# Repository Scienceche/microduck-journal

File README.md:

# 🦆 复刻 Microduck —— 项目日志仓库

对 [fanhao375/microduck-replica](https://github.com/fanhao375/microduck-replica) /
[OSHWhub imu_to_servo 团购板](https://oshwhub.com/team_wijnbslh/project_jhgdebrg) 的复刻实作记录：
一块自己焊的 IMU 总线板（STM32G031 + LSM6DSV16X + SN74LVC2G241）、一个 Radxa Zero 3W 主控、
15 颗飞特 HD1910、自训 RL 步态策略，以及把这一切调通的全部血泪。

> 私人仓库 · 每日自动同步自工作目录 `E:\c1349\复刻microduck`

## 当前状态（2026-11-06）

| 子系统 | 状态 |
|---|---|
| IMU 板（总线从机 ID 200 @1Mbps，FT6 协议） | ✅ 完全工作，装向四元数实测校准至 0.00° |
| 固件栈 | ✅ kissqy 官方栈 robotd 0.15.1（control.43）+ 三轮交叉编译热修复 |
| 总线质量 | ✅ 丢包 6-9% → 0.004%（ID12/13、ID34→10 两处时隙碰撞已断开） |
| 整机标定 | ✅ 15 舵机零位/方向/限位（标定台 :8085，robotd 桥接） |
| RL 训练（mjlab/MuJoCo Warp） | ✅ walk5 前进 0.19m/s；VelStand 抗扰站立 99% 存活（未部署） |
| 仿真保真 | ✅ 936g 整机质量 + 202g 电池（**含碰撞盒 70×38×35mm**，2026-11-06 起） |
| 步态/站立（kissqy 自训模型） | ✅ 满电+校向后 10 次冲击（翻滚/前冲/侧切/旋转）不倒 |
| 起身恢复 | ⏳ 测试中：门卫链路已打通，待满电跑 5 次推倒统计 |
| 摄像头（IMX219 CSI） | ✅ 单帧验证通过；mediad WebRTC 待装 GStreamer 栈 |
| 电源 | ⚠️ 2S 软包（7.72V@今晨）；峰值曾拉穿电压致整机重启，起身测试需满电 |

## 目录

```
docs/        调试记录（最重要的文件——完整故障树与修复过程）
firmware/    imu-to-ttl 固件（STM32G031 裸机，make g031-dxl）
hardware/    KiCad 复刻工程 + 元件手册
panel/       中控面板 duck_panel（旧栈）+ calib-panel 标定台（:8085，robotd 桥接）
sync.sh      每日同步脚本（工作目录 → 本仓库 → GitHub）
```

## 硬件速查

- **IMU 板**：团购 PCB + 克隆 STM32G031F8P6 + LSM6DSV16X（换过一颗，旧颗其实没坏）
- **舵机**：飞特 HD1910 ×15，ID 10-14 右腿 / 20-24 左腿 / 30-34 颈头嘴，IMU=200
- **接线**：imu-to-ttl 板自带 4 路舵机总线口 J_L/J_R/J_NECK/J_HEAD（丝印），比外接 hub 电流路径更均衡；
  dxl_hub（3 口无源）留作备用
- **电池**：2S 软包 70×38×35mm + 底座共 202g，装于躯干后下 (-0.027, 0, -0.055)；仿真已含碰撞盒
- 总线：飞特协议 1Mbps 半双工；U3=SN74LVC2G241（注意：**4脚是GND**，3脚=RX出，6脚=TX出）
- 已知坑：克隆 MCU 的 USART **DEM 硬件无效**（固件用软件 DE）；克隆批次 IMU 的 **SFLP 引擎输出乱转**
  （固件改软件 Mahony）；PB8/BOOT0 悬空随机进 bootloader（10k 拉带解决）

## 关键教训（详见调试记录）

1. 两层显示假象叠加可以完美伪装成"传感器坏轴"——用原始字节对质，不要信中间层
2. Mahony 积分项必须与比例项**同号相加**；接反=正反馈发散（主机回放 30 秒实锤）
3. 照抄参考代码写寄存器时，**核对每个地址和值的字面常量**（IF_CFG 0x02≠0x03 害人一整天）
4. 克隆 J-Link 自报产品名 "MS-ARGB"；WinUSB/WCID 一直在正常工作
5. Sync Read 相邻 ID 存在**应答时隙碰撞**（12→13、34→10 两处）：下一 ID 提前 1-2 比特应答污染上一 ID
   校验和。回包按 ID 解码与包序无关——换包序即可修复，硬件无需动
6. 仿真加配重**必须同时加碰撞几何**：只焊质量不焊盒子，策略对物理障碍"无感"，真机上脚怼进电池
7. IMU 装向校验要看**全重力向量**：gz 在小角度下与 0° 无异（cos8°=0.990），gx/gy 才暴露偏差
8. robotd 的标定/运动模式写进 systemd drop-in，**重启会继承**——"策略没反应"先查模式；
   init 不是起身控制器，趴姿 init 起不来

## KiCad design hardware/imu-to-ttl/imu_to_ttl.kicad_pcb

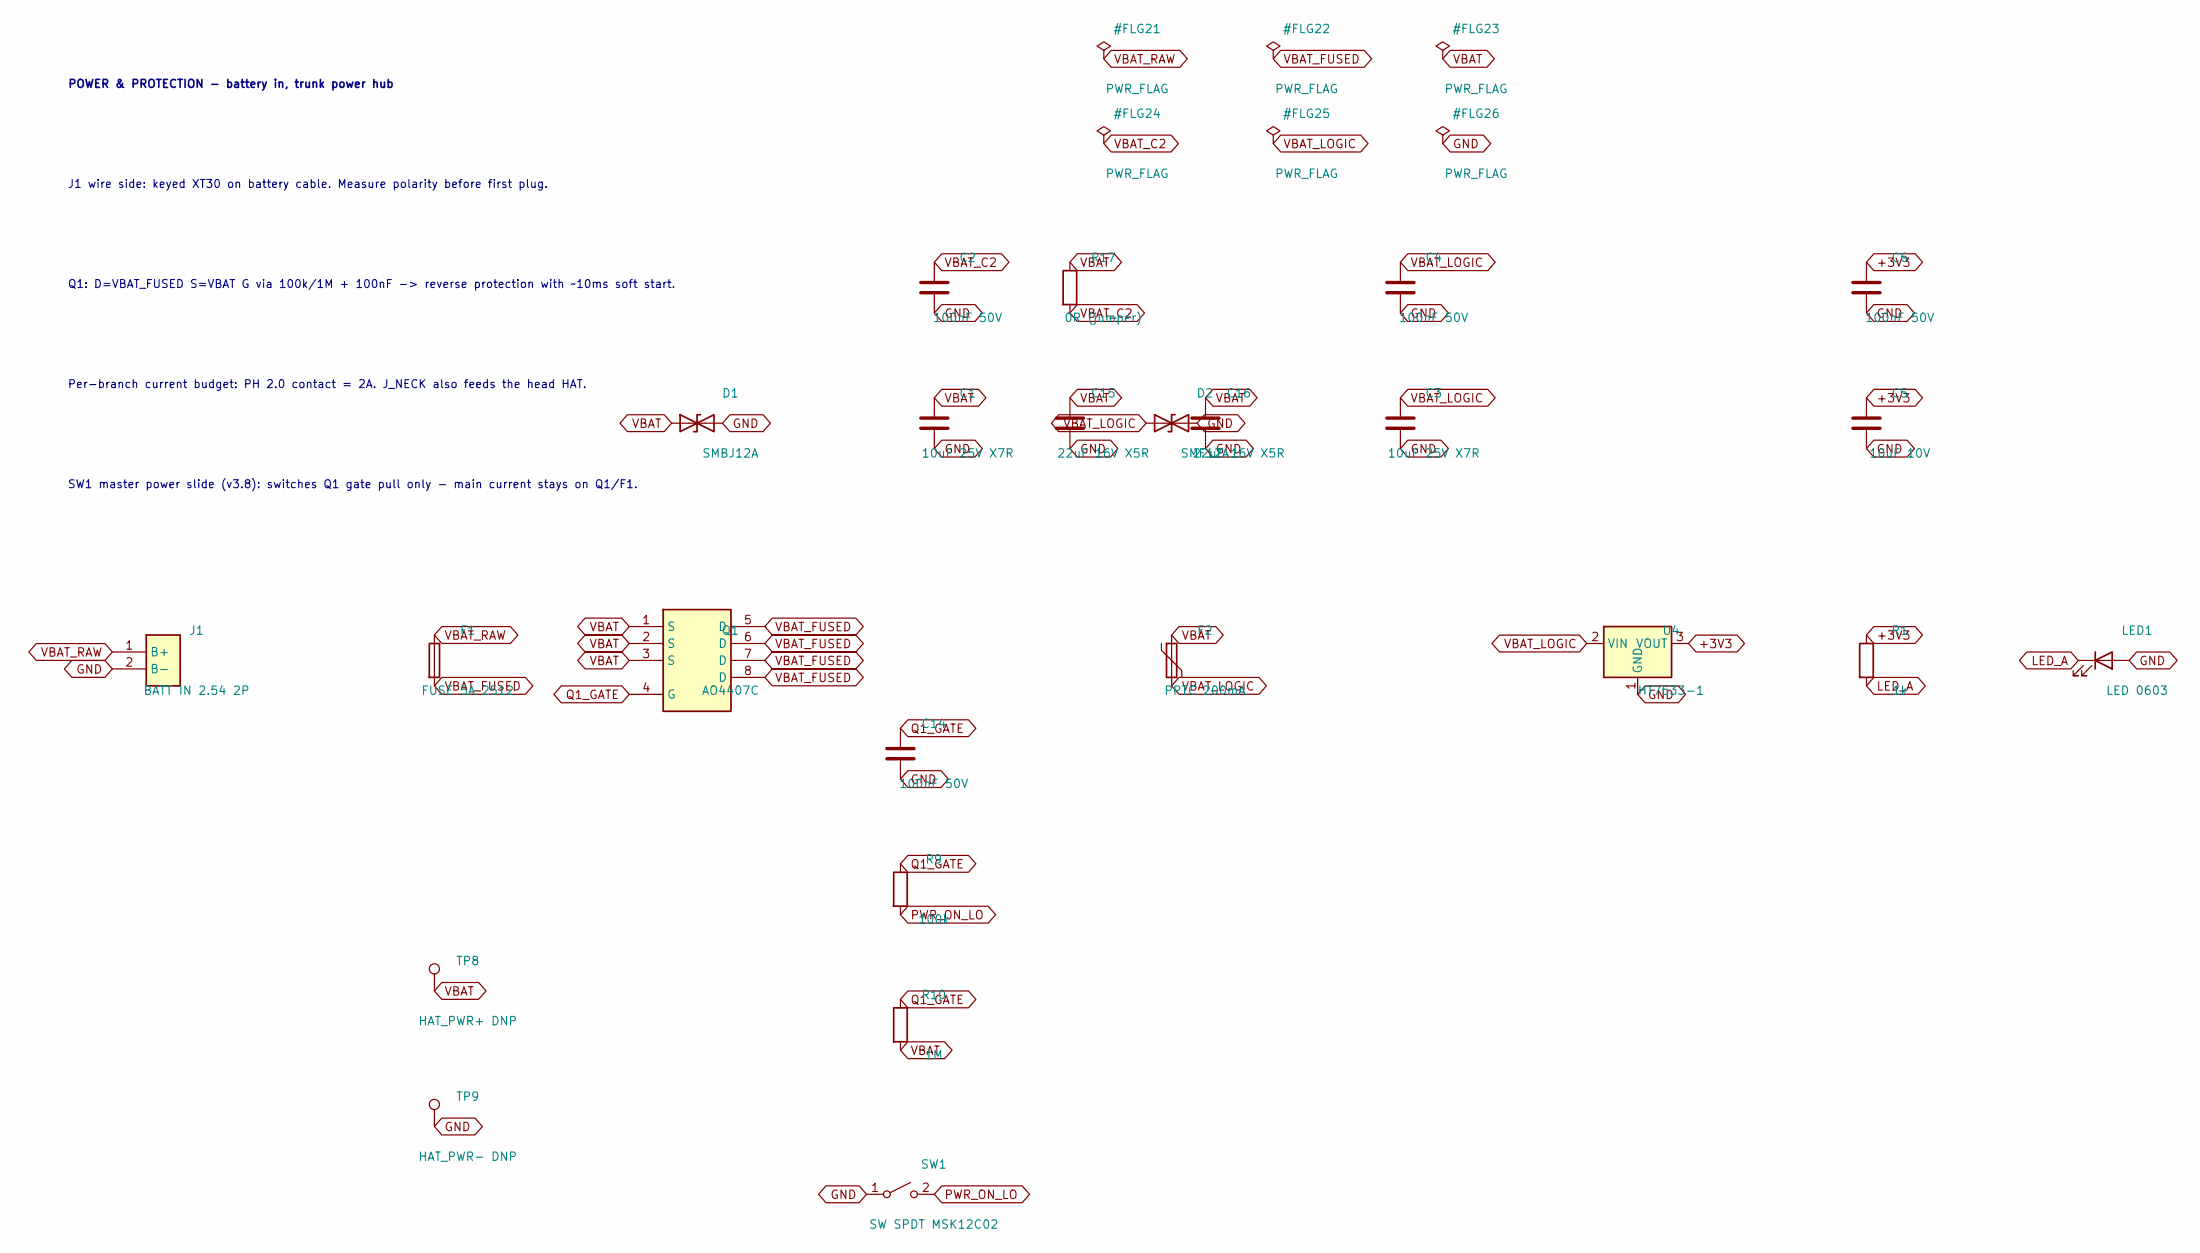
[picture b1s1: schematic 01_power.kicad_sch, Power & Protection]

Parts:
C1: 10uF 25V X7R; C_1206_3216Metric; MPN GRM31CR71E106KA12L; LCSC C77093
C2, C4, C6, C14: 100nF 50V; C_0603_1608Metric; MPN CC0603KRX7R9BB104; LCSC C14663
C3: 10uF 25V X7R; C_0805_2012Metric; MPN GRM31CR71E106KA12L; LCSC C77093
C5: 10uF 10V; C_0603_1608Metric; MPN CL10A106KP8NNNC; LCSC C19702
C15, C16: 22uF 16V X5R; C_1210_3225Metric; MPN EMK325BJ226KMHP; LCSC C359910
D1: SMBJ12A; D_SMB; MPN SMBJ12A/TR13; LCSC C111091
D2: SMF12A; D_SOD-123F; MPN SMF12A; LCSC C2943870
F1: FUSE 5A 2512; Fuse_1206_3216Metric; MPN 0466005.NRHF; LCSC C57525
F2: PPTC 200mA; Fuse_1206_3216Metric; MPN MF-NSMF020X-2; LCSC C210358
J1: BATT IN 2.54 2P; BattPad_1x02_P3.60mm_Drill1.2mm
LED1: LED 0603; LED_0603_1608Metric; MPN KT-0603R; LCSC C2286
Q1: AO4407C; SOIC-8_3.9x4.9mm_P1.27mm; MPN AO4407C; LCSC C469397
R1: 1k; R_0603_1608Metric; MPN 0603WAF1001T5E; LCSC C21190
R9: 100k; R_0603_1608Metric; MPN 0603WAF1003T5E; LCSC C25803
R10: 1M; R_0603_1608Metric; MPN 0603WAF1004T5E; LCSC C22935
R17: 0R (jumper); R_0603_1608Metric
SW1: SW SPDT MSK12C02; SW_SPDT_Shouhan_MSK12C02; MPN MSK12C02-LG; LCSC C431537
TP8: HAT_PWR+ DNP; TestPoint_Pad_D1.5mm
TP9: HAT_PWR- DNP; TestPoint_Pad_D1.5mm
U4: HT7533-1; SOT-89-3; MPN HT7533-1; LCSC C14289

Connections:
+3V3: C5.1, C6.1, R1.1, U4.3 (VOUT); also elsewhere on the board
GND: C1.2, C2.2, C3.2, C4.2, C5.2, C6.2, C14.2, C15.2, C16.2, D1.2 (A2), D2.2 (A2), J1.2 (B-), LED1.2 (A), SW1.1 (A), TP9.1, U4.1 (GND); also elsewhere on the board
LED_A: LED1.1 (K), R1.2
PWR_ON_LO: R9.2, SW1.2 (B)
Q1_GATE: C14.1, Q1.4 (G), R9.1, R10.1
VBAT: C1.1, C15.1, C16.1, D1.1 (A1), F2.1, Q1.1 (S), Q1.2 (S), Q1.3 (S), R10.2, R17.1, TP8.1; also elsewhere on the board
VBAT_C2: C2.1, R17.2
VBAT_FUSED: F1.2, Q1.5 (D), Q1.6 (D), Q1.7 (D), Q1.8 (D)
VBAT_LOGIC: C3.1, C4.1, D2.1 (A1), F2.2, U4.2 (VIN)
VBAT_RAW: F1.1, J1.1 (B+)

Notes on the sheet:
POWER & PROTECTION - battery in, trunk power hub
J1 wire side: keyed XT30 on battery cable. Measure polarity before first plug.
Q1: D=VBAT_FUSED S=VBAT G via 100k/1M + 100nF -> reverse protection with ~10ms soft start.
Per-branch current budget: PH 2.0 contact = 2A. J_NECK also feeds the head HAT.
SW1 master power slide (v3.8): switches Q1 gate pull only - main current stays on Q1/F1.

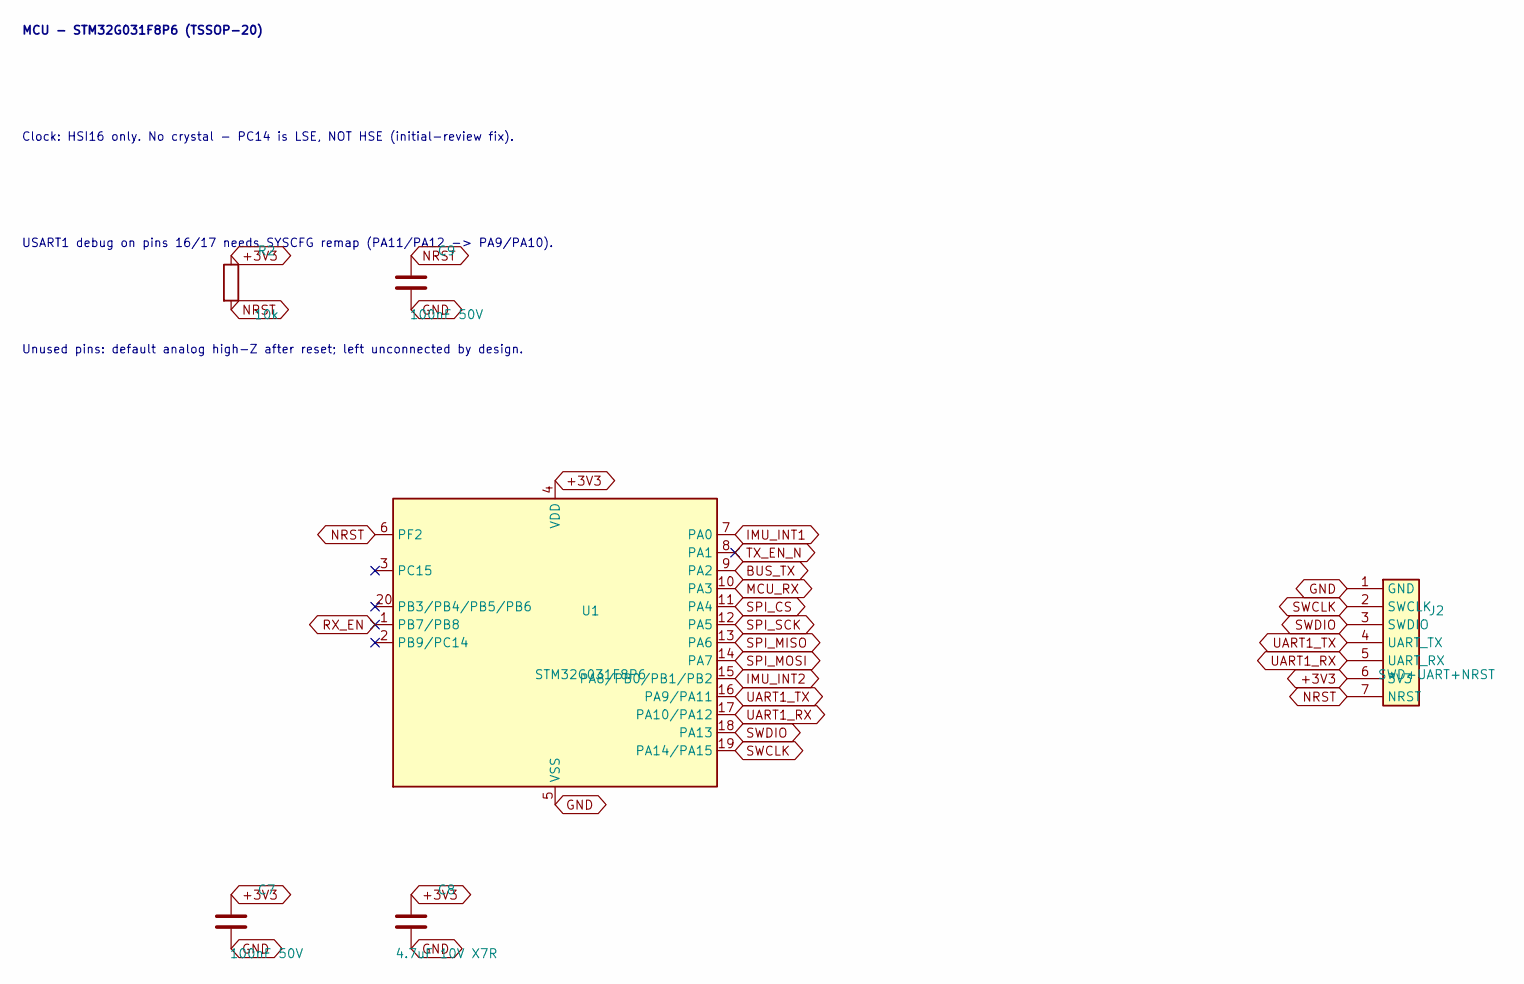
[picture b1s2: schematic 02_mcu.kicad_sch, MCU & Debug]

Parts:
C7, C9: 100nF 50V; C_0603_1608Metric; MPN CC0603KRX7R9BB104; LCSC C14663
C8: 4.7uF 10V X7R; C_0603_1608Metric; MPN CL10A475KO8NNNC; LCSC C19666
J2: SWD+UART+NRST; PinHeader_1x07_P2.54mm_Vertical; MPN PZ254R-11-07P; LCSC C492415
R2: 10k; R_0603_1608Metric; MPN 0603WAF1002T5E; LCSC C25804
U1: STM32G031F8P6; TSSOP-20_4.4x6.5mm_P0.65mm; MPN STM32G031F8P6; LCSC C529334

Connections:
+3V3: C7.1, C8.1, J2.6 (3V3), R2.1, U1.4 (VDD); also elsewhere on the board
BUS_TX: U1.9 (PA2); also elsewhere on the board
GND: C7.2, C8.2, C9.2, J2.1 (GND), U1.5 (VSS); also elsewhere on the board
IMU_INT1: U1.7 (PA0); also elsewhere on the board
IMU_INT2: U1.15 (PA8/PB0/PB1/PB2); also elsewhere on the board
MCU_RX: U1.10 (PA3); also elsewhere on the board
NRST: C9.1, J2.7 (NRST), R2.2, U1.6 (PF2)
RX_EN: U1.1 (PB7/PB8); also elsewhere on the board
SPI_CS: U1.11 (PA4); also elsewhere on the board
SPI_MISO: U1.13 (PA6); also elsewhere on the board
SPI_MOSI: U1.14 (PA7); also elsewhere on the board
SPI_SCK: U1.12 (PA5); also elsewhere on the board
SWCLK: J2.2 (SWCLK), U1.19 (PA14/PA15)
SWDIO: J2.3 (SWDIO), U1.18 (PA13)
TX_EN_N: U1.8 (PA1); also elsewhere on the board
UART1_RX: J2.5 (UART_RX), U1.17 (PA10/PA12)
UART1_TX: J2.4 (UART_TX), U1.16 (PA9/PA11)

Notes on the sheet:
MCU - STM32G031F8P6 (TSSOP-20)
Clock: HSI16 only. No crystal - PC14 is LSE, NOT HSE (initial-review fix).
USART1 debug on pins 16/17 needs SYSCFG remap (PA11/PA12 -> PA9/PA10).
Unused pins: default analog high-Z after reset; left unconnected by design.

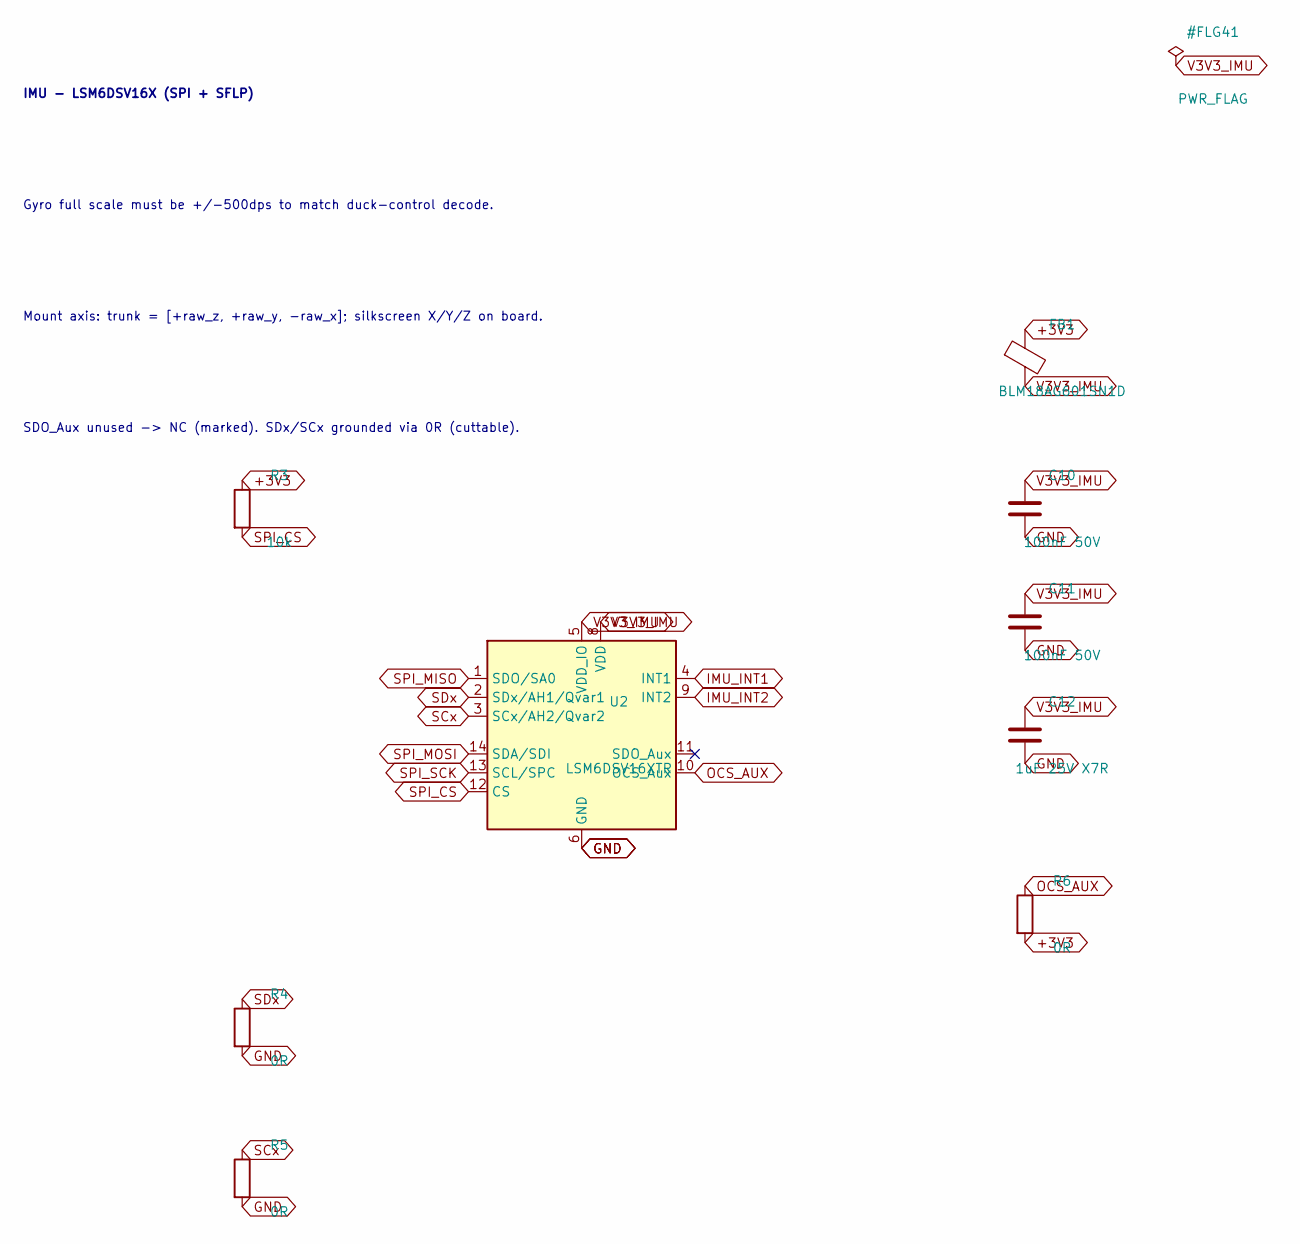
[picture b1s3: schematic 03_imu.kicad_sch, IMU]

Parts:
C10, C11: 100nF 50V; C_0603_1608Metric; MPN CC0603KRX7R9BB104; LCSC C14663
C12: 1uF 25V X7R; C_0603_1608Metric; MPN CL10B105KA8NNNC; LCSC C29936
FB1: BLM18AG601SN1D; L_0603_1608Metric; MPN BLM18AG601SN1D; LCSC C19330
R3: 10k; R_0603_1608Metric; MPN 0603WAF1002T5E; LCSC C25804
R4, R5, R6: 0R; R_0603_1608Metric; MPN 0603WAF0000T5E; LCSC C21189
U2: LSM6DSV16XTR; ST_LGA14_3x2.5_P0.5_LSM6DSV16X_TN0018; MPN LSM6DSV16XTR; LCSC C5267406

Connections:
+3V3: FB1.1, R3.1, R6.2; also elsewhere on the board
GND: C10.2, C11.2, C12.2, R4.2, R5.2, U2.6 (GND), U2.7 (GND); also elsewhere on the board
IMU_INT1: U2.4 (INT1); also elsewhere on the board
IMU_INT2: U2.9 (INT2); also elsewhere on the board
OCS_AUX: R6.1, U2.10 (OCS_Aux)
SCx: R5.1, U2.3 (SCx/AH2/Qvar2)
SDx: R4.1, U2.2 (SDx/AH1/Qvar1)
SPI_CS: R3.2, U2.12 (CS); also elsewhere on the board
SPI_MISO: U2.1 (SDO/SA0); also elsewhere on the board
SPI_MOSI: U2.14 (SDA/SDI); also elsewhere on the board
SPI_SCK: U2.13 (SCL/SPC); also elsewhere on the board
V3V3_IMU: C10.1, C11.1, C12.1, FB1.2, U2.5 (VDD_IO), U2.8 (VDD)

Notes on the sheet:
IMU - LSM6DSV16X (SPI + SFLP)
Gyro full scale must be +/-500dps to match duck-control decode.
Mount axis: trunk = [+raw_z, +raw_y, -raw_x]; silkscreen X/Y/Z on board.
SDO_Aux unused -> NC (marked). SDx/SCx grounded via 0R (cuttable).

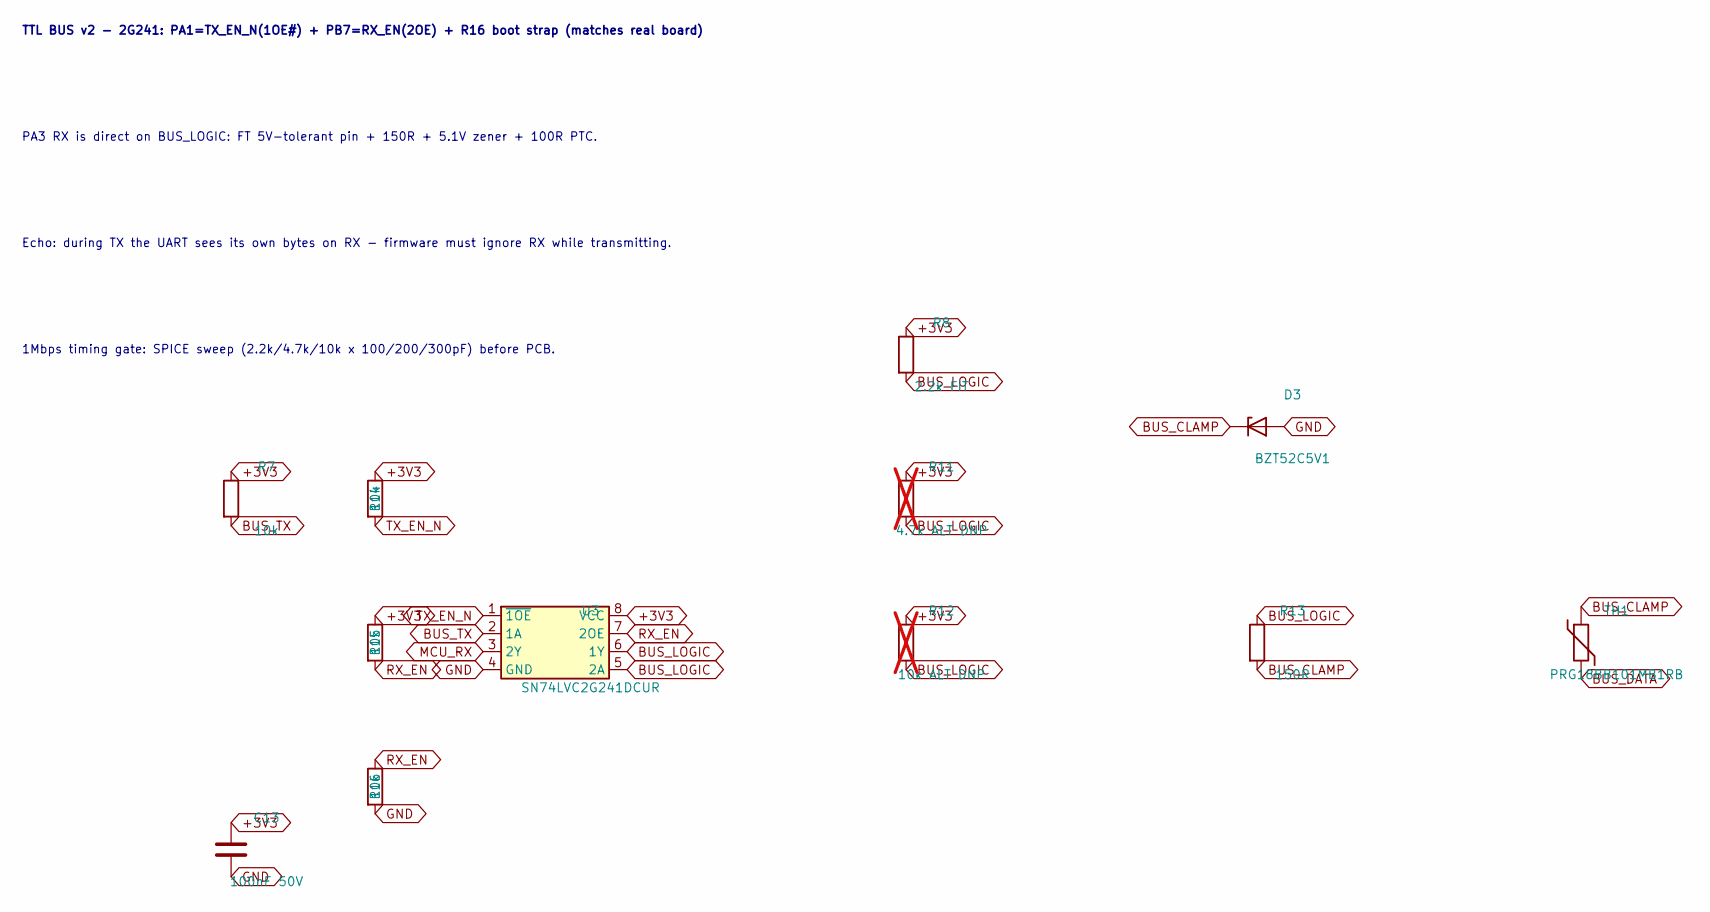
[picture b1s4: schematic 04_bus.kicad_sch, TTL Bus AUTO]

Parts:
C13: 100nF 50V; C_0603_1608Metric; MPN CC0603KRX7R9BB104; LCSC C14663
D3: BZT52C5V1; D_SOD-323; MPN BZT52C5V1-7-F; LCSC C151588
R7: 10k; R_0603_1608Metric; MPN 0603WAF1002T5E; LCSC C25804
R8: 2.2k FIT; R_0603_1608Metric; MPN 0603WAF2201T5E; LCSC C4190
R11: 4.7k ALT DNP; R_0603_1608Metric; MPN 0603WAF4701T5E; LCSC C23162; not fitted
R12: 10k ALT DNP; R_0603_1608Metric; MPN 0603WAF1002T5E; LCSC C25804; not fitted
R13: 150R; R_0603_1608Metric; MPN 0603WAF1500T5E; LCSC C22808
R14, R15, R16: 10k; R_0603_1608Metric
TH1: PRG18BB101MB1RB; R_0603_1608Metric; MPN PRG18BB101MB1RB; LCSC C913703
U3: SN74LVC2G241DCUR; VSSOP-8_2.3x2mm_P0.5mm; MPN SN74LVC2G241DCUR; LCSC C10430

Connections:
+3V3: C13.1, R7.1, R8.1, R11.1, R12.1, R14.1, R15.1, U3.8 (VCC); also elsewhere on the board
BUS_CLAMP: D3.1 (K), R13.2, TH1.1
BUS_DATA: TH1.2; also elsewhere on the board
BUS_LOGIC: R8.2, R11.2, R12.2, R13.1, U3.5 (2A), U3.6 (1Y)
BUS_TX: R7.2, U3.2 (1A); also elsewhere on the board
GND: C13.2, D3.2 (A), R16.2, U3.4 (GND); also elsewhere on the board
MCU_RX: U3.3 (2Y); also elsewhere on the board
RX_EN: R15.2, R16.1, U3.7 (2OE); also elsewhere on the board
TX_EN_N: R14.2, U3.1 (~1OE); also elsewhere on the board

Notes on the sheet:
TTL BUS v2 - 2G241: PA1=TX_EN_N(1OE#) + PB7=RX_EN(2OE) + R16 boot strap (matches real board)
PA3 RX is direct on BUS_LOGIC: FT 5V-tolerant pin + 150R + 5.1V zener + 100R PTC.
Echo: during TX the UART sees its own bytes on RX - firmware must ignore RX while transmitting.
1Mbps timing gate: SPICE sweep (2.2k/4.7k/10k x 100/200/300pF) before PCB.

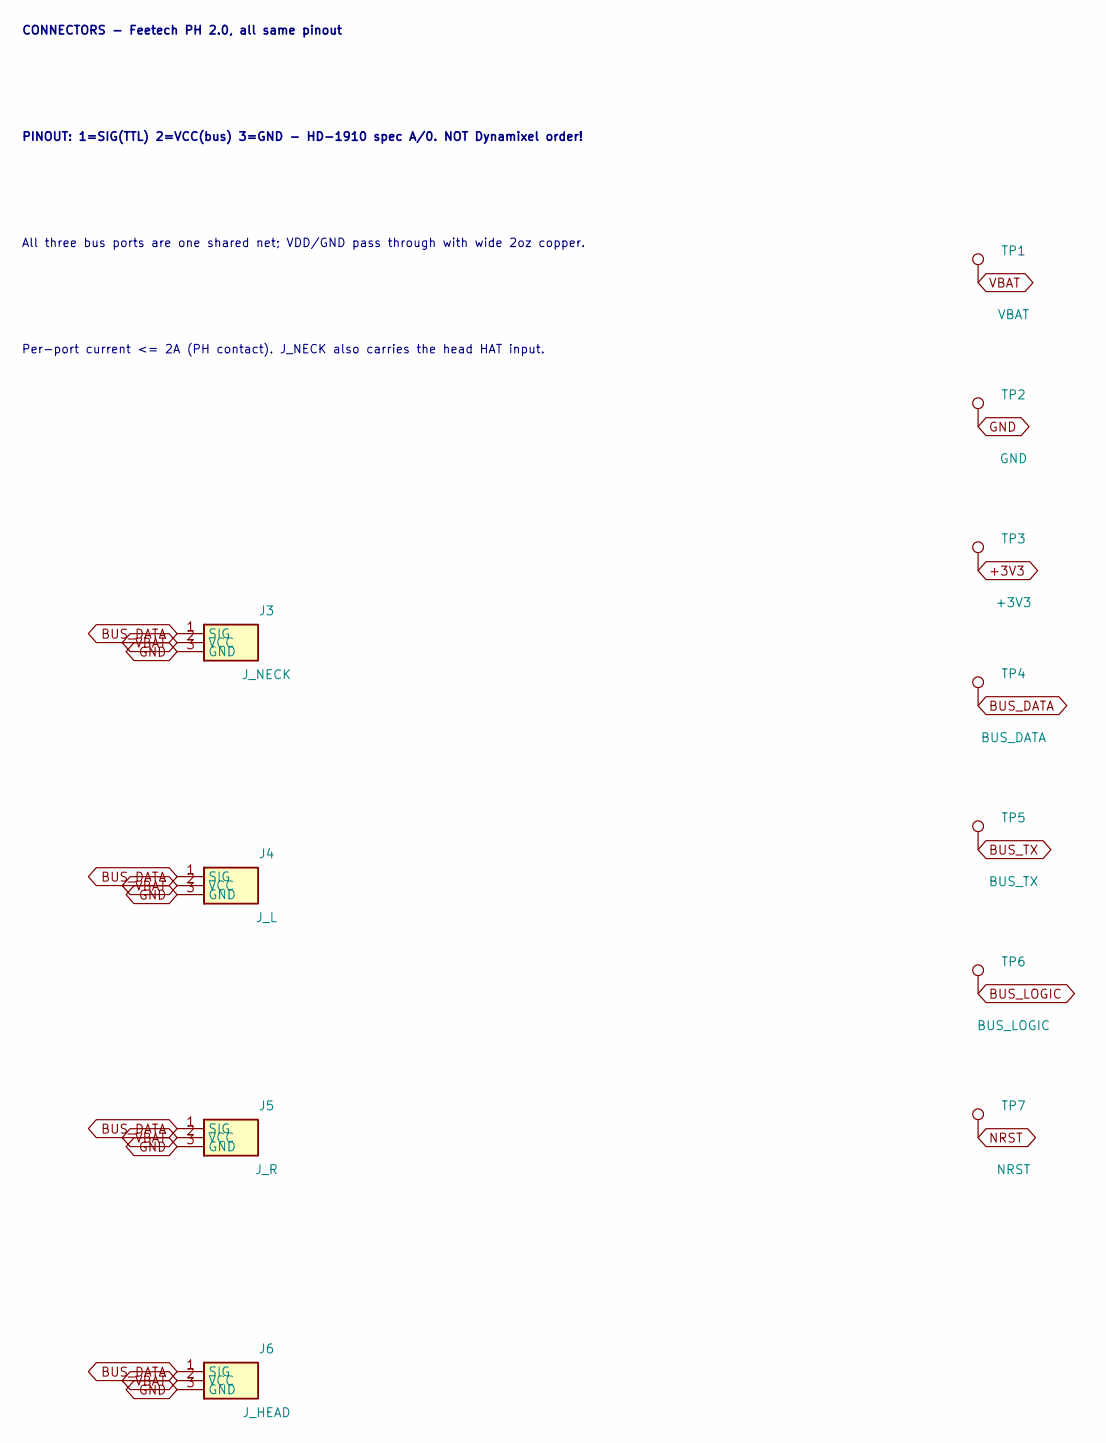
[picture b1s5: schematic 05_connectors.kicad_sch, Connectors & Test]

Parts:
J3: J_NECK; CONN-TH_B3B-PH-K-S; MPN B3B-PH-K-S(LF)(SN); LCSC C131339
J4: J_L; CONN-TH_S3B-PH-K-S; MPN S3B-PH-K-S(LF)(SN); LCSC C169277
J5: J_R; CONN-TH_S3B-PH-K-S; MPN S3B-PH-K-S(LF)(SN); LCSC C169277
J6: J_HEAD; CONN-TH_B3B-PH-K-S; MPN B3B-PH-K-S(LF)(SN); LCSC C131339
TP1: VBAT; TestPoint_Pad_D1.0mm
TP2: GND; TestPoint_Pad_D1.0mm
TP3: +3V3; TestPoint_Pad_D1.0mm
TP4: BUS_DATA; TestPoint_Pad_D1.0mm
TP5: BUS_TX; TestPoint_Pad_D1.0mm
TP6: BUS_LOGIC; TestPoint_Pad_D1.0mm
TP7: NRST; TestPoint_Pad_D1.0mm

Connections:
+3V3: TP3.1; also elsewhere on the board
BUS_DATA: J3.1 (SIG), J4.1 (SIG), J5.1 (SIG), J6.1 (SIG), TP4.1; also elsewhere on the board
GND: J3.3 (GND), J4.3 (GND), J5.3 (GND), J6.3 (GND), TP2.1; also elsewhere on the board
VBAT: J3.2 (VCC), J4.2 (VCC), J5.2 (VCC), J6.2 (VCC), TP1.1; also elsewhere on the board

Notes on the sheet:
CONNECTORS - Feetech PH 2.0, all same pinout
PINOUT: 1=SIG(TTL) 2=VCC(bus) 3=GND - HD-1910 spec A/0. NOT Dynamixel order!
All three bus ports are one shared net; VDD/GND pass through with wide 2oz copper.
Per-port current <= 2A (PH contact). J_NECK also carries the head HAT input.

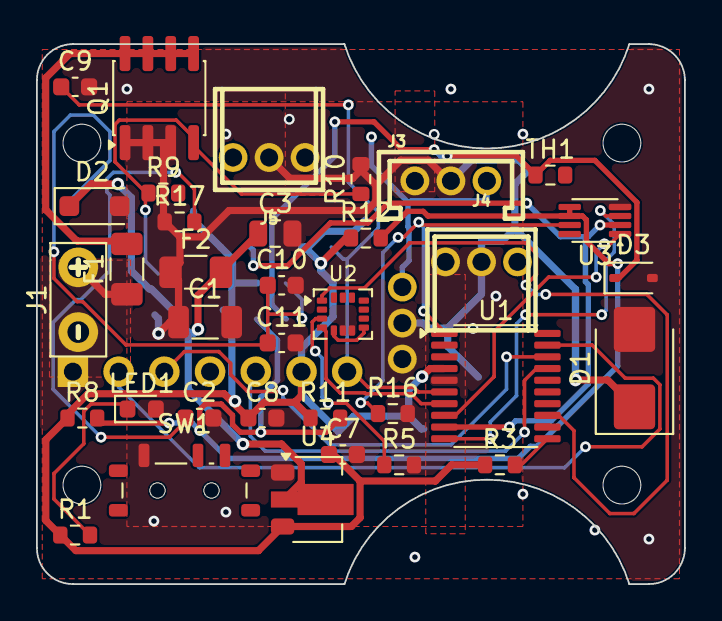
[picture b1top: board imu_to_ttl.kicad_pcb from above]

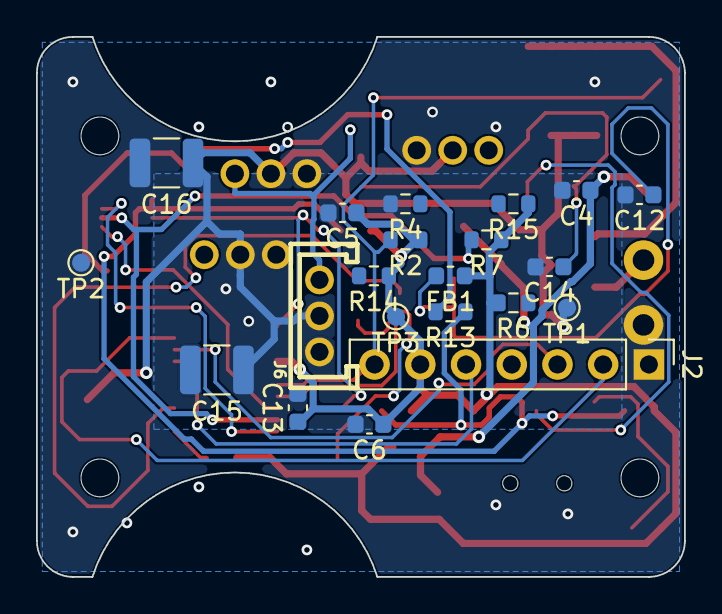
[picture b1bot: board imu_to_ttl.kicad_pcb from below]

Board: 2 copper layers, 36.0 x 30.0 mm, 60 parts (21 on the bottom side), 32 nets.

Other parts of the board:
M1, M2, M3, M4: M2; MountingHole_2.1mm_M2

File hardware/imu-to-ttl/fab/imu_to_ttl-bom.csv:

Value,Side,Qty
0R,top,3
100k,top,1
100nF 50V,bottom,3
100nF 50V,top,6
10k,bottom,1
10k,top,5
10k ALT DNP,bottom,1
10uF 10V,bottom,1
10uF 25V X7R,bottom,1
10uF 25V X7R,top,1
150R,bottom,1
1M,top,1
1k,bottom,1
1uF 25V X7R,top,1
2.2k FIT,top,1
4.7k ALT DNP,bottom,1
4.7uF 10V X7R,bottom,1
AO4407C,top,1
BATT IN 2.54 2P,top,1
BLM18AG601SN1D,top,1
BZT52C5V1,top,1
FUSE 5A 2512,top,1
HT7533-1,bottom,1
J_L,top,1
J_NECK,top,1
J_R,top,1
LED 0603,bottom,1
LSM6DSV16XTR,top,1
PPTC 200mA,bottom,1
PRG18BB101MB1RB,bottom,1
SMBJ12A,top,1
SMF12A,bottom,1
SN74LVC2G241DCUR,top,1
STM32G031F8P6,top,1
SWD+UART+NRST,top,1

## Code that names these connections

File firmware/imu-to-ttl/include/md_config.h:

#pragma once
#include <stdint.h>
#include <stddef.h>
#include <stdbool.h>

#ifdef __cplusplus
extern "C" {
#endif

/* Host contract - unchanged from the DXL version so host decode stays valid */
#define MD_IMU_ID               200u      /* Feetech slave ID */
#define MD_IMU_BAUD             1000000u
#define MD_IMU_READ_ADDR        124u      /* 0x7C: 12-byte block */
#define MD_IMU_BLOCK_LEN        12u
#define MD_IMU_DIAG_LEN         8u
#define MD_IMU_MODEL_NUMBER     10200u
#define MD_IMU_FW_VERSION       2u      /* v2.x: 看门狗+复位诊断+版本可观测(每次发版必改) */
#define MD_IMU_FW_MINOR         4u      /* v2.4: 开机信标也门控(reg150),上电完全静默 */

/* Control table covering addr 0 .. 143 */
#define MD_CTRL_TABLE_SIZE      152u

/* Feetech STS memory-map offsets used for identity */
#define MD_FT_ADDR_FW_MAJOR     0u
#define MD_FT_ADDR_FW_MINOR     1u
#define MD_FT_ADDR_END          2u
#define MD_FT_ADDR_ID           5u
#define MD_FT_ADDR_BAUD         6u
#define MD_FT_ADDR_RETURN_DELAY 7u
#define MD_FT_ADDR_STATUS_LEVEL 8u
#define MD_FT_BAUD_CODE_1M      0u

/*
 * Board pin map - imu_to-ttl v1.0.
 * AUTO bus (no DE / no RX_EN): PA2 TX drives 1G125 A and /OE; PA3 RX taps
 * the bus directly (FT pin, 150R + 5.1V zener + 100R PTC).
 *
 * Variant for the imu_to_dxl / OSHWhub "imu_to_servo" board: build with
 * -DMD_BUS_DE=1. That board drives the bus through an SN74LVC2G241 whose
 * TX buffer enable 1OE# (active low, "DE" net) sits on PA1. PA1 AF1 is
 * USART2_RTS_DE_CK (DS12992 Rev 4, Table 12), so USART2 hardware driver
 * enable does the direction switching: CR3 DEM=1, DEP=1 (DE low while
 * transmitting). R4 pulls 1OE# high, keeping the board silent on the bus
 * whenever it is not transmitting. The RX buffer (2OE) stays enabled via
 * R7, so the local-echo discard path below is unchanged.
 */
#define MD_PIN_IMU_INT          0u   /* PA0  <- LSM6 INT1 (optional) */
#define MD_PIN_USART2_TX        2u   /* PA2  AF1 -> 1G125 / 2G241 1A */
#define MD_PIN_USART2_RX        3u   /* PA3  AF1 <- bus */
#ifdef MD_BUS_DE
#define MD_PIN_USART2_DE        1u   /* PA1  AF1 = USART2_RTS_DE_CK -> 2G241 1OE# (low = TX on) */
#endif
#define MD_PIN_SPI_CS           4u   /* PA4 */
#define MD_PIN_SPI_SCK          5u   /* PA5  AF0 */
#define MD_PIN_SPI_MISO         6u   /* PA6  AF0 */
#define MD_PIN_SPI_MOSI         7u   /* PA7  AF0 */
#define MD_PIN_USART1_TX        11u  /* PA11 -> debug header pin 4 (SYSCFG remap to PA9) */
#define MD_PIN_USART1_RX        12u  /* PA12 <- debug header pin 5 (SYSCFG remap to PA10) */
#define MD_PIN_SWDIO            13u
#define MD_PIN_SWCLK            14u

/* Gyro full-scale for packing - match duck-control +/-500 dps */
#define MD_GYRO_FS_DPS          500

/* 诊断寄存器（控制表 144..151 空闲区，152 为表尾） */
#define MD_REG_RESET_FLAGS      144u  /* bit0=IWDG bit1=WWDG bit2=SFT bit3=PWR(POR/BOR) bit4=PIN bit5=OBL */
#define MD_REG_RESET_COUNT      145u  /* IWDG 复位计数（noinit RAM，断电清零） */
#define MD_REG_WDT_TEST         146u  /* 写 0xA5 → 停喂看门狗 → ~1.5s 后 IWDG 复位（在线自证） */
#define MD_REG_BUILD_DATE       147u  /* 3 字节 yy mm dd 构建日期——"板上到底跑的哪版"一读便知 */
#define MD_REG_HEARTBEAT_EN     150u  /* 心跳信标开关:0=关(默认,防上电窗口干扰主机) 1=开 */

#ifdef __cplusplus
}
#endif

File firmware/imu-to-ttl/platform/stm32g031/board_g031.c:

/**
 * STM32G031F8P6 board layer - IMU-to-TTL v1.0.
 * AUTO half-duplex bus: PA2 (USART2_TX) drives 1G125 A + /OE; PA3 is RX
 * tapped directly on the bus (FT pin, 150R + 5.1V zener + 100R PTC).
 * Local echo of our own transmission is discarded at the ISR level.
 */
#include "board.h"
#include "md_config.h"
#include <stddef.h>
#include <stdint.h>
#include <stdbool.h>

#if defined(MD_PLATFORM_STM32G031)

#define PERIPH_BASE        0x40000000u
#define AHBPERIPH_BASE     (PERIPH_BASE + 0x00020000u)
#define RCC_BASE           (AHBPERIPH_BASE + 0x00001000u)
#define GPIOA_BASE         0x50000000u  /* IOPORT region on STM32G0 */

#define USART2_BASE        (PERIPH_BASE + 0x00004400u)
#define SPI1_BASE          (PERIPH_BASE + 0x00013000u)

#define RCC_IOPENR         (*(volatile uint32_t *)(RCC_BASE + 0x34u))
#define RCC_APBENR1        (*(volatile uint32_t *)(RCC_BASE + 0x3Cu))
#define RCC_APBENR2        (*(volatile uint32_t *)(RCC_BASE + 0x40u))

#define GPIOA_MODER        (*(volatile uint32_t *)(GPIOA_BASE + 0x00u))
#define GPIOA_OSPEEDR      (*(volatile uint32_t *)(GPIOA_BASE + 0x08u))
#define GPIOA_AFRL         (*(volatile uint32_t *)(GPIOA_BASE + 0x20u))
#define GPIOA_BSRR         (*(volatile uint32_t *)(GPIOA_BASE + 0x18u))

#define USART_CR1          (*(volatile uint32_t *)(USART2_BASE + 0x00u))
#define USART_CR3          (*(volatile uint32_t *)(USART2_BASE + 0x08u))
#define USART_BRR          (*(volatile uint32_t *)(USART2_BASE + 0x0Cu))
#define USART_ISR          (*(volatile uint32_t *)(USART2_BASE + 0x1Cu))
#define USART_RDR          (*(volatile uint32_t *)(USART2_BASE + 0x24u))
#define USART_TDR          (*(volatile uint32_t *)(USART2_BASE + 0x28u))

#define NVIC_ISER0         (*(volatile uint32_t *)0xE000E100u)

#define SPI_CR1            (*(volatile uint32_t *)(SPI1_BASE + 0x00u))
#define SPI_CR2            (*(volatile uint32_t *)(SPI1_BASE + 0x04u))
#define SPI_SR             (*(volatile uint32_t *)(SPI1_BASE + 0x08u))
#define SPI_DR             (*(volatile uint32_t *)(SPI1_BASE + 0x0Cu))

#ifndef MD_PLATFORM_IRQ_USART2
#define MD_PLATFORM_IRQ_USART2 28u
#endif

#define PIN_MODER(pin, mode) \
    do { \
        GPIOA_MODER = (GPIOA_MODER & ~(3u << ((pin) * 2))) | ((uint32_t)(mode) << ((pin) * 2)); \
    } while (0)

static volatile uint32_t g_ms;
static volatile uint8_t g_rx_q[64];
static volatile uint8_t g_rx_r, g_rx_w;
static volatile bool g_tx_active;
static volatile uint32_t g_echo_dropped;

void SysTick_Handler(void)
{
    g_ms++;
}

/* USART2 IRQ: enqueue received bytes, drop the local echo while transmitting. */
void USART2_IRQHandler(void)
{
    uint32_t isr = USART_ISR;
    /* 错误标志清刷:ORE/FE/NE 滞留会堵死接收路径(上电总线毛刺的典型后遗症)。
     * G0 USART_ISR: FE=bit1 NE=bit2 ORE=bit3;ICR 写 1 清除(已对 CMSIS 头核对)。 */
    if (isr & ((1u << 3) | (1u << 2) | (1u << 1))) {
        (*(volatile uint32_t *)(USART2_BASE + 0x20u)) = (1u << 3) | (1u << 2) | (1u << 1); /* ICR */
        if (isr & (1u << 5)) {
            (void)USART_RDR; /* 清残留数据 */
        }
        return;
    }
    if (isr & (1u << 5)) { /* RXNE */
        uint8_t b = (uint8_t)USART_RDR;
        if (g_tx_active) {
            g_echo_dropped++;
        } else {
            uint8_t next = (uint8_t)((g_rx_w + 1u) & 63u);
            if (next != g_rx_r) {
                g_rx_q[g_rx_w] = b;
                g_rx_w = next;
            }
        }
    }
}

static void gpio_init(void)
{
    RCC_IOPENR |= (1u << 0); /* GPIOA */

    /* PA0 IMU_INT input (reserved) */
    PIN_MODER(MD_PIN_IMU_INT, 0);

    /* PA4 SPI CS output high */
    PIN_MODER(MD_PIN_SPI_CS, 1);
    GPIOA_BSRR = (1u << MD_PIN_SPI_CS);

    /* PB7/PB8 (U1.1, RX_EN net): drive HIGH after boot. The board straps this
     * pin to GND through 10k so the (option-byte-less clone) MCU reliably
     * boots from flash; without this drive the strap would hold the bus
     * transceiver's 2OE low and leave the board deaf. */
    {
        #define GPIOB_BASE_ 0x50000400u
        #define GPIOB_MODER_ (*(volatile uint32_t *)(GPIOB_BASE_ + 0x00u))
        #define GPIOB_BSRR_  (*(volatile uint32_t *)(GPIOB_BASE_ + 0x18u))
        RCC_IOPENR |= (1u << 1);              /* GPIOB clock */
        GPIOB_MODER_ = (GPIOB_MODER_ & ~(3u << 7 * 2)) | (1u << 7 * 2); /* PB7 out */
        GPIOB_BSRR_ = (1u << 7);              /* high = receive enable */
    }

    /* PA2/PA3 AF1 USART2 */
    PIN_MODER(MD_PIN_USART2_TX, 2);
    PIN_MODER(MD_PIN_USART2_RX, 2);
    GPIOA_AFRL = (GPIOA_AFRL & ~(0xFFu << (MD_PIN_USART2_TX * 4))) |
                 (0x11u << (MD_PIN_USART2_TX * 4));
#ifdef MD_BUS_DE
    /* PA1 -> U3.1 1OE# (low = transmit enable), software-driven: the clone
     * MCU's USART2 has no working DEM (DE output never asserts, and DEAT/DEDT
     * refuse to write), so the hardware DE mode cannot be used. */
    PIN_MODER(MD_PIN_USART2_DE, 1);
    GPIOA_BSRR = (1u << MD_PIN_USART2_DE); /* high = TX disabled at idle */
#endif

    /* PA5/6/7 AF0 SPI1 */
    PIN_MODER(MD_PIN_SPI_SCK, 2);
    PIN_MODER(MD_PIN_SPI_MISO, 2);
    PIN_MODER(MD_PIN_SPI_MOSI, 2);
    GPIOA_AFRL &= ~((0xFul << (MD_PIN_SPI_SCK * 4)) |
                    (0xFul << (MD_PIN_SPI_MISO * 4)) |
                    (0xFul << (MD_PIN_SPI_MOSI * 4)));
    GPIOA_OSPEEDR |= (3u << (MD_PIN_SPI_SCK * 2)) | (3u << (MD_PIN_SPI_MOSI * 2));
}

static void usart2_init(void)
{
    RCC_APBENR1 |= (1u << 17); /* USART2EN */
    USART_CR1 = 0;
    USART_CR3 = 0; /* no DEM: direction pin is software-driven (clone MCU) */
    USART_BRR = 16; /* 16 MHz HSI / 1 Mbps */
    USART_CR1 = (1u << 5) | (1u << 3) | (1u << 2) | (1u << 0); /* RXNEIE TE RE UE */
    NVIC_ISER0 = (1u << MD_PLATFORM_IRQ_USART2);
}

static void spi1_init(void)
{
    RCC_APBENR2 |= (1u << 12); /* SPI1EN */
    SPI_CR1 = 0;
    SPI_CR1 = (1u << 2) | (1u << 8) | (1u << 9) | (2u << 3); /* MSTR SSM SSI BR/8 */
    /* DS=8bit + FRXTH: RXNE at 1-byte FIFO level. Without FRXTH, RXNE only
     * asserts at the 16-bit level and a single 8-bit transfer never completes
     * - spi_xfer spins forever on real silicon (Renode's SPI model does not
     * reproduce the FIFO threshold, so the gate missed it). */
    SPI_CR2 = (7u << 8) | (1u << 12);
    SPI_CR1 |= (1u << 6); /* SPE */
}

static uint8_t spi_xfer(uint8_t v)
{
    while ((SPI_SR & (1u << 1)) == 0) {
    }
    *(volatile uint8_t *)&SPI_DR = v;
    while ((SPI_SR & (1u << 0)) == 0) {
    }
    return *(volatile uint8_t *)&SPI_DR;
}

void board_init(void)
{
    /* Vector table lives in main flash. On real silicon VTOR=0 works because
     * flash is aliased at 0x00000000, but set it explicitly: same code path
     * regardless of boot config, and required under emulation. */
    *(volatile uint32_t *)0xE000ED08u = 0x08000000u; /* SCB->VTOR */

    gpio_init();
    usart2_init();
    spi1_init();
    /* SysTick 1 ms at 16 MHz */
    *(volatile uint32_t *)0xE000E014u = 16000u - 1u; /* LOAD */
    *(volatile uint32_t *)0xE000E018u = 0;           /* clear current value */
    *(volatile uint32_t *)0xE000E010u = 7u;          /* enable, core clock, IRQ */
    g_ms = 0;
    g_rx_r = g_rx_w = 0;
}

void board_delay_ms(uint32_t ms)
{
    uint32_t start = g_ms;
    while ((g_ms - start) < ms) {
    }
}

uint32_t board_millis(void)
{
    return g_ms;
}

void board_idle(void)
{
    __asm__ volatile("wfi");
}

void board_bus_write(const uint8_t *data, size_t len)
{
    g_tx_active = true;
#ifdef MD_BUS_DE
    GPIOA_BSRR = (1u << (MD_PIN_USART2_DE + 16)); /* 1OE# low: drive the bus */
#endif
    for (size_t i = 0; i < len; i++) {
        while ((USART_ISR & (1u << 7)) == 0) {
        }
        USART_TDR = data[i];
    }
    while ((USART_ISR & (1u << 6)) == 0) {
    } /* TC */
    /* window for the trailing echo byte to be dropped by the ISR */
    for (volatile uint32_t i = 0; i < 40u; i++) {
    }
#ifdef MD_BUS_DE
    GPIOA_BSRR = (1u << MD_PIN_USART2_DE); /* 1OE# high: release the bus */
#endif
    /* flush anything that still made it into the queue */
    while (USART_ISR & (1u << 5)) {
        (void)USART_RDR;
    }
    g_tx_active = false;
}

bool board_bus_read_byte(uint8_t *out)
{
    if (g_rx_r == g_rx_w) {
        return false;
    }
    *out = g_rx_q[g_rx_r];
    g_rx_r = (uint8_t)((g_rx_r + 1u) & 63u);
    return true;
}

int32_t board_imu_spi_write(void *user, uint8_t reg, const uint8_t *data, uint16_t len)
{
    (void)user;
    GPIOA_BSRR = (1u << (MD_PIN_SPI_CS + 16));
    (void)spi_xfer((uint8_t)(reg & 0x7Fu));
    for (uint16_t i = 0; i < len; i++) {
        (void)spi_xfer(data[i]);
    }
    GPIOA_BSRR = (1u << MD_PIN_SPI_CS);
    return 0;
}

int32_t board_imu_spi_read(void *user, uint8_t reg, uint8_t *data, uint16_t len)
{
    (void)user;
    GPIOA_BSRR = (1u << (MD_PIN_SPI_CS + 16));
    (void)spi_xfer((uint8_t)(reg | 0x80u));
    for (uint16_t i = 0; i < len; i++) {
        data[i] = spi_xfer(0xFFu);
    }
    GPIOA_BSRR = (1u << MD_PIN_SPI_CS);
    return 0;
}

#else
/* Non-G031 translation unit placeholder - host platform supplies board_*. */
#endif
